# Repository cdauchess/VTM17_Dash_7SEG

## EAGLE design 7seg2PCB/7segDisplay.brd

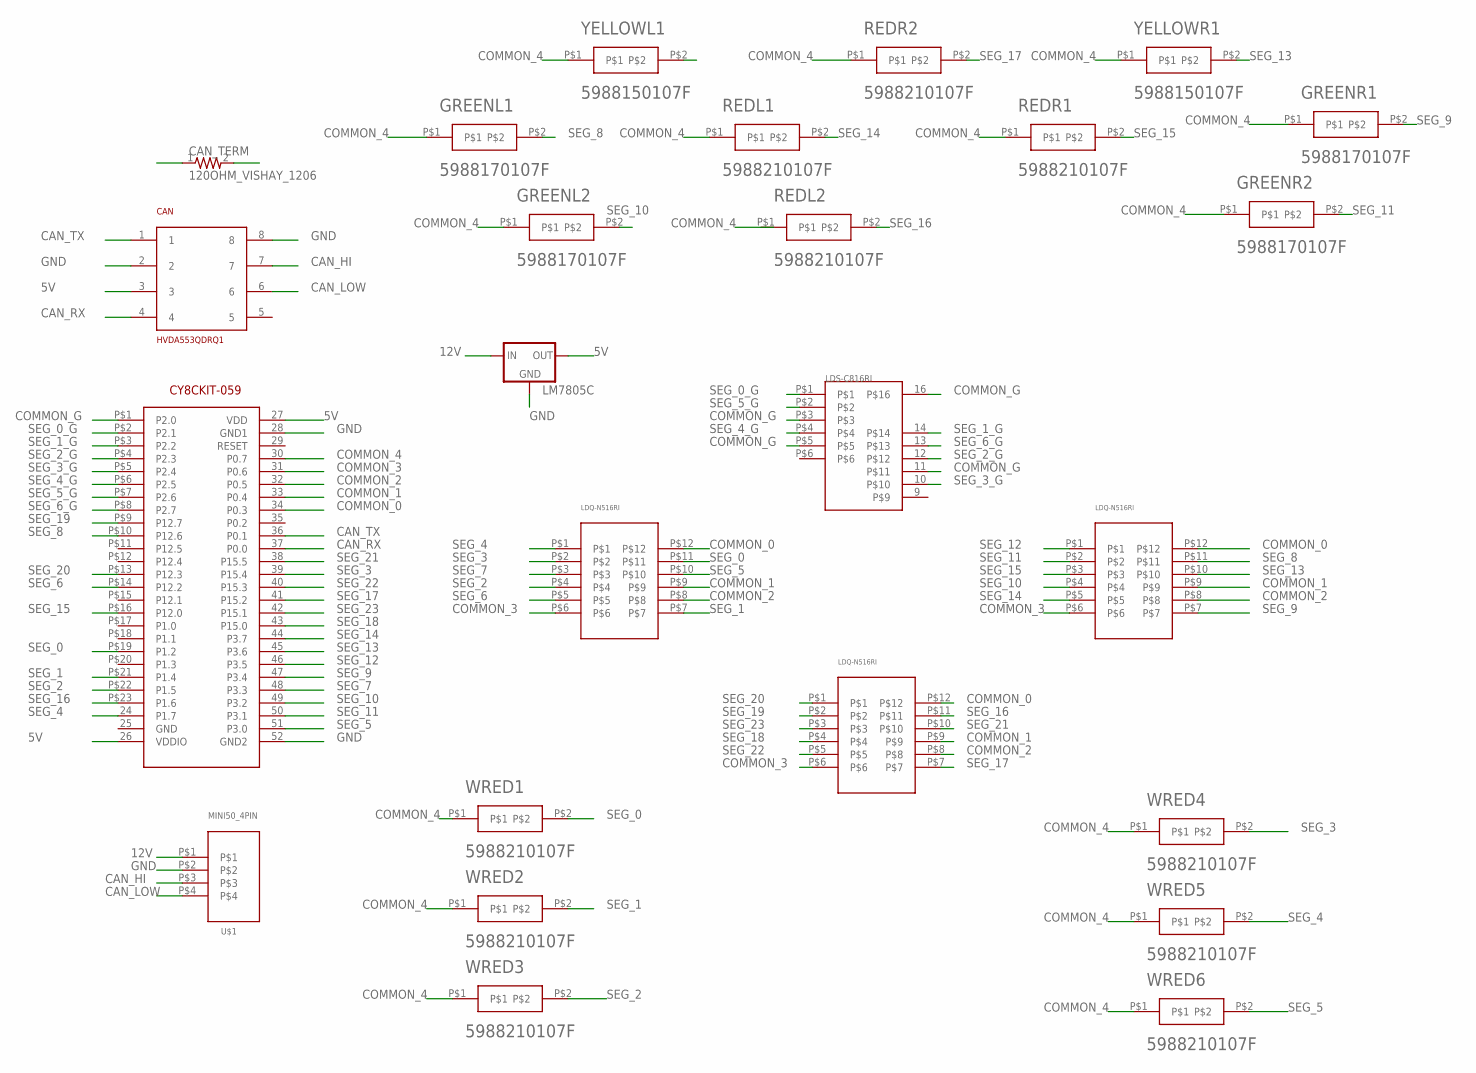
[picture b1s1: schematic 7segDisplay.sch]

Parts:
BOTTOM: LDQ-N516RI
CAN: HVDA553QDRQ1; SOIC127P600X172-8N
CAN_TERM: 120OHM_VISHAY_1206; 1206
GEAR: LDS-C816RITHROUGH_HOLE; LDS-C816RI
GREENL1, GREENL2: 5988170107F; 0805
GREENR1, GREENR2: 5988170107F; 0805
LEFT: LDQ-N516RI
LM7805C: 78XXL
REDL1, REDL2: 5988210107F; 1206
REDR1, REDR2: 5988210107F; 1206
RIGHT: LDQ-N516RI
U$1: MINI50_4PIN; 34792-0041
U$3: CY8CKIT-059
WRED1, WRED2, WRED3, WRED4, WRED5, WRED6: 5988210107F; 1206
YELLOWL1: 5988150107F; 0805
YELLOWR1: 5988150107F; 0805

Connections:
5V: CAN.3, LM7805C.OUT, U$3.26 (VDDIO), U$3.27 (VDD)
12V: LM7805C.IN, U$1.P$1
CAN_HI: CAN.7, CAN_TERM.1, U$1.P$3
CAN_LOW: CAN.6, CAN_TERM.2, U$1.P$4
CAN_RX: CAN.4, U$3.37 (P0.0)
CAN_TX: CAN.1, U$3.36 (P0.1)
COMMON_0: BOTTOM.P$12, LEFT.P$12, RIGHT.P$12, U$3.34 (P0.3)
COMMON_1: BOTTOM.P$9, LEFT.P$9, RIGHT.P$9, U$3.33 (P0.4)
COMMON_2: BOTTOM.P$8, LEFT.P$8, RIGHT.P$8, U$3.32 (P0.5)
COMMON_3: BOTTOM.P$6, LEFT.P$6, RIGHT.P$6, U$3.31 (P0.6)
COMMON_4: GREENL1.P$1, GREENL2.P$1, GREENR1.P$1, GREENR2.P$1, REDL1.P$1, REDR1.P$1, REDR2.P$1, U$3.30 (P0.7), WRED1.P$1, WRED2.P$1, WRED3.P$1, WRED4.P$1, WRED5.P$1, WRED6.P$1, YELLOWL1.P$1, YELLOWR1.P$1
COMMON_G: GEAR.11, GEAR.16, GEAR.P$3, GEAR.P$5, U$3.P$1 (P2.0)
GND: CAN.2, CAN.8, LM7805C.GND, U$1.P$2, U$3.28 (GND1), U$3.52 (GND2)
SEG_0: LEFT.P$11, U$3.P$19 (P1.2), WRED1.P$2
SEG_0_G: GEAR.P$1, U$3.P$2 (P2.1)
SEG_1: LEFT.P$7, U$3.P$21 (P1.4), WRED2.P$2
SEG_1_G: GEAR.14, U$3.P$3 (P2.2)
SEG_2: LEFT.P$4, U$3.P$22 (P1.5), WRED3.P$2
SEG_2_G: GEAR.12, U$3.P$4 (P2.3)
SEG_3: LEFT.P$2, U$3.39 (P15.4), WRED4.P$2
SEG_3_G: GEAR.10, U$3.P$5 (P2.4)
SEG_4: LEFT.P$1, U$3.24 (P1.7), WRED5.P$2
SEG_4_G: GEAR.P$4, U$3.P$6 (P2.5)
SEG_5: LEFT.P$10, U$3.51 (P3.0), WRED6.P$2
SEG_5_G: GEAR.P$2, U$3.P$7 (P2.6)
SEG_6: LEFT.P$5, U$3.P$14 (P12.2)
SEG_6_G: GEAR.13, U$3.P$8 (P2.7)
SEG_7: LEFT.P$3, U$3.48 (P3.3)
SEG_8: GREENL1.P$2, RIGHT.P$11, U$3.P$10 (P12.6)
SEG_9: GREENR1.P$2, RIGHT.P$7, U$3.47 (P3.4)
SEG_10: GREENL2.P$2, RIGHT.P$4, U$3.49 (P3.2)
SEG_11: GREENR2.P$2, RIGHT.P$2, U$3.50 (P3.1)
SEG_12: RIGHT.P$1, U$3.46 (P3.5), YELLOWL1.P$2
SEG_13: RIGHT.P$10, U$3.45 (P3.6), YELLOWR1.P$2
SEG_14: REDL1.P$2, RIGHT.P$5, U$3.44 (P3.7)
SEG_15: REDR1.P$2, RIGHT.P$3, U$3.P$16 (P12.0)
SEG_16: BOTTOM.P$11, REDL2.P$2, U$3.P$23 (P1.6)
SEG_17: BOTTOM.P$7, REDR2.P$2, U$3.41 (P15.2)
SEG_18: BOTTOM.P$4, U$3.43 (P15.0)
SEG_19: BOTTOM.P$2, U$3.P$9 (P12.7)
SEG_20: BOTTOM.P$1, U$3.P$13 (P12.3)
SEG_21: BOTTOM.P$10, U$3.38 (P15.5)
SEG_22: BOTTOM.P$5, U$3.40 (P15.3)
SEG_23: BOTTOM.P$3, U$3.42 (P15.1)

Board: 2 copper layers, 25 parts (5 on the bottom side), 44 nets, no tracks yet.

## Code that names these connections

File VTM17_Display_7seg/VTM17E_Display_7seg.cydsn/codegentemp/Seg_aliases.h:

/*******************************************************************************
* File Name: Seg.h  
* Version 2.20
*
* Description:
*  This file contains the Alias definitions for Per-Pin APIs in cypins.h. 
*  Information on using these APIs can be found in the System Reference Guide.
*
* Note:
*
********************************************************************************
* Copyright 2008-2015, Cypress Semiconductor Corporation.  All rights reserved.
* You may use this file only in accordance with the license, terms, conditions, 
* disclaimers, and limitations in the end user license agreement accompanying 
* the software package with which this file was provided.
*******************************************************************************/

#if !defined(CY_PINS_Seg_ALIASES_H) /* Pins Seg_ALIASES_H */
#define CY_PINS_Seg_ALIASES_H

#include "cytypes.h"
#include "cyfitter.h"


/***************************************
*              Constants        
***************************************/
#define Seg_0			(Seg__0__PC)
#define Seg_0_INTR	((uint16)((uint16)0x0001u << Seg__0__SHIFT))

#define Seg_1			(Seg__1__PC)
#define Seg_1_INTR	((uint16)((uint16)0x0001u << Seg__1__SHIFT))

#define Seg_2			(Seg__2__PC)
#define Seg_2_INTR	((uint16)((uint16)0x0001u << Seg__2__SHIFT))

#define Seg_3			(Seg__3__PC)
#define Seg_3_INTR	((uint16)((uint16)0x0001u << Seg__3__SHIFT))

#define Seg_4			(Seg__4__PC)
#define Seg_4_INTR	((uint16)((uint16)0x0001u << Seg__4__SHIFT))

#define Seg_5			(Seg__5__PC)
#define Seg_5_INTR	((uint16)((uint16)0x0001u << Seg__5__SHIFT))

#define Seg_6			(Seg__6__PC)
#define Seg_6_INTR	((uint16)((uint16)0x0001u << Seg__6__SHIFT))

#define Seg_7			(Seg__7__PC)
#define Seg_7_INTR	((uint16)((uint16)0x0001u << Seg__7__SHIFT))

#define Seg_8			(Seg__8__PC)
#define Seg_8_INTR	((uint16)((uint16)0x0001u << Seg__8__SHIFT))

#define Seg_9			(Seg__9__PC)
#define Seg_9_INTR	((uint16)((uint16)0x0001u << Seg__9__SHIFT))

#define Seg_10			(Seg__10__PC)
#define Seg_10_INTR	((uint16)((uint16)0x0001u << Seg__10__SHIFT))

#define Seg_11			(Seg__11__PC)
#define Seg_11_INTR	((uint16)((uint16)0x0001u << Seg__11__SHIFT))

#define Seg_12			(Seg__12__PC)
#define Seg_12_INTR	((uint16)((uint16)0x0001u << Seg__12__SHIFT))

#define Seg_13			(Seg__13__PC)
#define Seg_13_INTR	((uint16)((uint16)0x0001u << Seg__13__SHIFT))

#define Seg_14			(Seg__14__PC)
#define Seg_14_INTR	((uint16)((uint16)0x0001u << Seg__14__SHIFT))

#define Seg_15			(Seg__15__PC)
#define Seg_15_INTR	((uint16)((uint16)0x0001u << Seg__15__SHIFT))

#define Seg_16			(Seg__16__PC)
#define Seg_16_INTR	((uint16)((uint16)0x0001u << Seg__16__SHIFT))

#define Seg_17			(Seg__17__PC)
#define Seg_17_INTR	((uint16)((uint16)0x0001u << Seg__17__SHIFT))

#define Seg_18			(Seg__18__PC)
#define Seg_18_INTR	((uint16)((uint16)0x0001u << Seg__18__SHIFT))

#define Seg_19			(Seg__19__PC)
#define Seg_19_INTR	((uint16)((uint16)0x0001u << Seg__19__SHIFT))

#define Seg_20			(Seg__20__PC)
#define Seg_20_INTR	((uint16)((uint16)0x0001u << Seg__20__SHIFT))

#define Seg_21			(Seg__21__PC)
#define Seg_21_INTR	((uint16)((uint16)0x0001u << Seg__21__SHIFT))

#define Seg_22			(Seg__22__PC)
#define Seg_22_INTR	((uint16)((uint16)0x0001u << Seg__22__SHIFT))

#define Seg_23			(Seg__23__PC)
#define Seg_23_INTR	((uint16)((uint16)0x0001u << Seg__23__SHIFT))

#define Seg_INTR_ALL	 ((uint16)(Seg_0_INTR| Seg_1_INTR| Seg_2_INTR| Seg_3_INTR| Seg_4_INTR| Seg_5_INTR| Seg_6_INTR| Seg_7_INTR| Seg_8_INTR| Seg_9_INTR| Seg_10_INTR| Seg_11_INTR| Seg_12_INTR| Seg_13_INTR| Seg_14_INTR| Seg_15_INTR| Seg_16_INTR| Seg_17_INTR| Seg_18_INTR| Seg_19_INTR| Seg_20_INTR| Seg_21_INTR| Seg_22_INTR| Seg_23_INTR))

#endif /* End Pins Seg_ALIASES_H */


/* [] END OF FILE */

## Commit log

2016-10-11 :neckbeard: Added .gitattributes & .gitignore files
2016-10-11 Initial Push
2016-10-17 CAN Functions
    The code receives the messages. Need to set up other message IDs and
    parse the data to prepare it for display
2016-10-19 7seg/can parse
    Currently this code drives a single 7 seg display for understanding of
    how to interact with the display. The can parsing function is mostly
    complete, just need to go through and verify all of the scaling values
    and variable types for each data point.
2016-10-24 VTM17DashV1
    Data indication on the 3 4digit displays works, need to add gear
    indication, and shift+warning lights.
2016-10-28 Updated Code, Added PCB files to this folder
2016-10-30 Updated code, added NX Models
2016-11-03 Added Button Code
    Added a function to check the button input and switch states when
    appropriate. No debouncing needed currently because the button has a
    very clean make - May need with other buttons
2016-11-07 Added Gear Calculation
    This is untested, will be tested on the car in the Spring. The
    algorithim is validated only with previous data in matlab currently.
2016-11-14 Shift Light Function
    The Shift light function is in progress currently, need to figure out
    the loop bounds to get the correct lights to illuminate.
2016-11-14 Shift Light Function Works
    Removed loops and hardcoded which lights will be on or off -> this
    works. Need to further investigate loop bounds when I have more time ->
    Maybe in the spring
2016-11-14 Added Offset Flashing
    Flashing for shift light is now offset with the center 2 on while the
    outer 8 are off.
2016-11-14 Moved Functions to external file
    This cleaned up the main file and improved readability by adding a
    header file with function prototypes
2016-11-15 Warning Light Function
    The function for managing the warning lights is working well.
2017-01-24 Added EV
    Added EV project to file, CAN parsing for EV
2017-04-05 Updated EV Code
    This code is what was tested on the EV on 4/4/17. Only the VMC30 was
    online. Had to change the conditions to enter the CAN parse function
    because only VMC30 was present on the CAN bus
2017-04-20 Another EV Update
    Now updates display if any data is available, not if all is available.
    May need to force a slower update rate or set motor RPM to 0 if below 0.
2017-05-05 Code for EV and Combustion Driving
    Gear Works on Combustion

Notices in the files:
parts and their libraries:
SparkFun-Resistors: Licensing: Creative Commons ShareAlike 4.0 International - https://creativecommons.org/licenses/by-sa/4.0
